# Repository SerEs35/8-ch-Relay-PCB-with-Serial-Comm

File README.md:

# 8-ch-Relay-PCB-with-Serial-Comm

About this project:
----
This was a project done during undergraduate studies. It is a PCB, operated by a 16F84A microcontroller connected to the computer via Serial Port. The relays can be activated from the computer, and it is only one-way transmission.

The documents in this repository are listed as follows:

\schema_8relay.sch
>Contains the schematic of the circuit, performed in Eagle Cadsoft

\schema_8relay.brd
>Contains the layout of the circuit, performed in Eagle Cadsoft

\project.asm
>Contains the source code in ASM language for the microcontroller

\Serial_rs232.zip
>Contains the source code project for the GUI coded in C# with MS Visual Studio 2003

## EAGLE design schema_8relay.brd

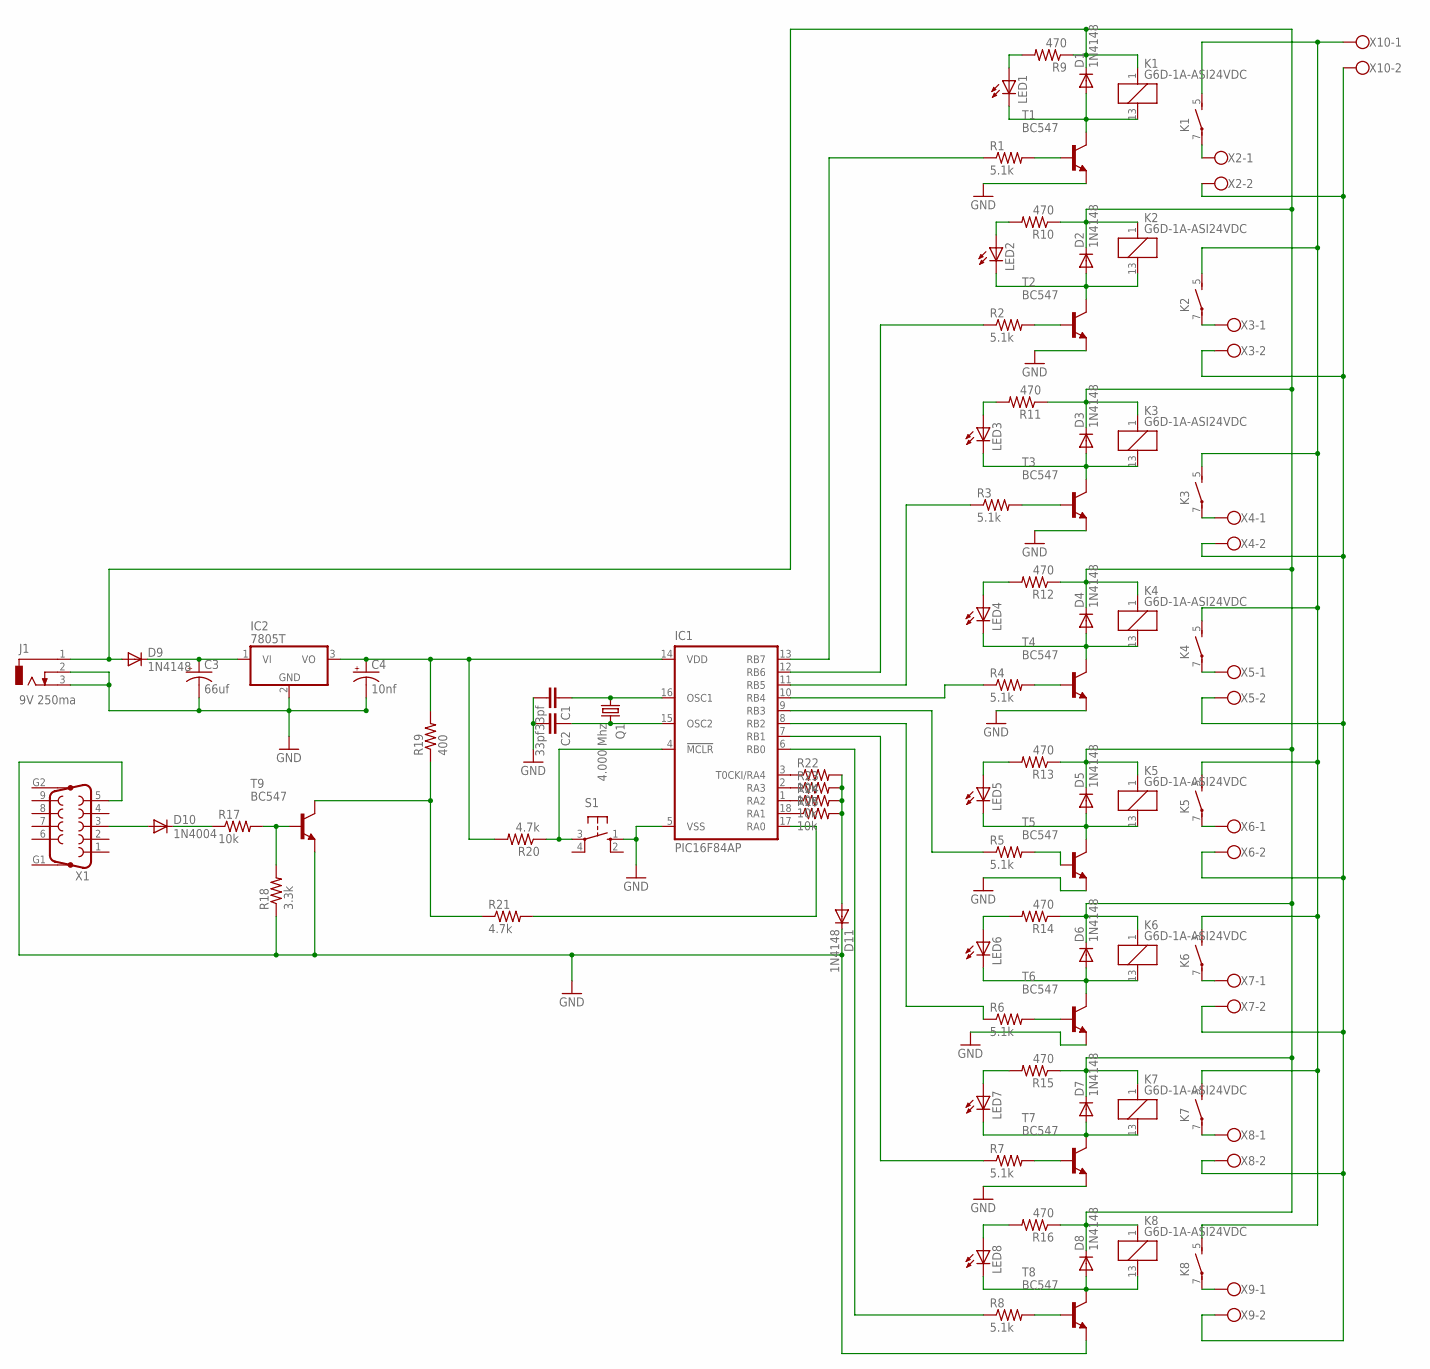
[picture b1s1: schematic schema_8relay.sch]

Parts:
C1, C2: 33pf; C050-024X044
C3: 66uf; E2,5-6
C4: 10nf; E2,5-6
D1, D2, D3, D4, D5, D6, D7, D8, D9, D11: 1N4148; DO35-10
D10: 1N4004; DO41-10
IC1: PIC16F84AP; DIL18
IC2: 7805T; TO220H
J1: 9V 250ma; DCJ0303
K1, K2, K3, K4, K5, K6, K7, K8: G6D-1A-ASI24VDC; G6D
LED1, LED2, LED3, LED4, LED5, LED6, LED7, LED8: LED3MM
Q1: 4.000 Mhz; HC49U70
R1, R2, R3, R4, R5, R6, R7, R8: 5.1k; 0204/7
R9, R10, R11, R12, R13, R14, R15, R16: 470; 0204/7
R17, R22, R23, R24, R25: 10k; 0204/7
R18: 3.3k; 0204/7
R19: 400; 0207/12
R20, R21: 4.7k; 0204/7
S1: 10-XX; B3F-10XX
T1, T2, T3, T4, T5, T6, T7, T8, T9: BC547; TO92
X1: F09HP
X2, X3, X4, X5, X6, X7, X8, X9, X10: W237-102

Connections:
GND: C1.2, C2.2, C3.-, C4.-, D11.C, IC1.5 (VSS), IC2.2 (GND), J1.2, J1.3, R18.1, S1.1 (S), T1.1 (E), T2.1 (E), T3.1 (E), T4.1 (E), T5.1 (E), T6.1 (E), T7.1 (E), T8.1 (E), T9.1 (E), X1.5
unnamed: C1.1, IC1.16 (OSC1), Q1.1
unnamed: C2.1, IC1.15 (OSC2), Q1.2
unnamed: R19.1, R21.1, T9.3 (C)
unnamed: D1.A, K1.13 (2), LED1.K (C), T1.3 (C)
unnamed: R1.2, T1.2 (B)
unnamed: D2.A, K2.13 (2), LED2.K (C), T2.3 (C)
unnamed: IC1.17 (RA0), R21.2
unnamed: IC1.4 (!MCLR), R20.1, S1.3
unnamed: D10.A, X1.3
unnamed: D10.C, R17.1
unnamed: R17.2, R18.2, T9.2 (B)
unnamed: C4.+, IC1.14 (VDD), IC2.3 (VO), R19.2, R20.2
unnamed: IC1.13 (RB7), R1.1
unnamed: K1.7, X2.1
unnamed: R2.2, T2.2 (B)
unnamed: LED2.A, R10.2
unnamed: D4.A, K4.13 (2), LED4.K (C), T4.3 (C)
unnamed: D6.A, K6.13 (2), LED6.K (C), T6.3 (C)
unnamed: LED4.A, R12.2
unnamed: K2.7, X3.1
unnamed: IC1.10 (RB4), R4.1
unnamed: R3.2, T3.2 (B)
unnamed: R5.2, T5.2 (B)
unnamed: LED5.A, R13.2
unnamed: K3.7, X4.1
unnamed: IC1.9 (RB3), R5.1
unnamed: R4.2, T4.2 (B)
unnamed: LED6.A, R14.2
unnamed: LED3.A, R11.2
unnamed: K4.7, X5.1
unnamed: K1.5 (S), K2.5 (S), K3.5 (S), K4.5 (S), K5.5 (S), K6.5 (S), K7.5 (S), K8.5 (S), X10.1
unnamed: C3.+, D9.C, IC2.1 (VI)
unnamed: K5.7, X6.1
unnamed: IC1.3 (T0CKI/RA4), R22.1
unnamed: R6.2, T6.2 (B)
unnamed: IC1.2 (RA3), R23.1
unnamed: K6.7, X7.1
unnamed: IC1.1 (RA2), R24.1
unnamed: R7.2, T7.2 (B)
unnamed: D7.A, K7.13 (2), LED7.K (C), T7.3 (C)
unnamed: IC1.18 (RA1), R25.1
unnamed: K7.7, X8.1
unnamed: D5.A, K5.13 (2), LED5.K (C), T5.3 (C)
unnamed: R8.2, T8.2 (B)
unnamed: LED8.A, R16.2
unnamed: LED7.A, R15.2
unnamed: K8.7, X9.1
unnamed: IC1.6 (RB0), R8.1
unnamed: IC1.7 (RB1), R7.1
unnamed: IC1.8 (RB2), R6.1
unnamed: D8.A, K8.13 (2), LED8.K (C), T8.3 (C)
unnamed: LED1.A, R9.2
unnamed: IC1.11 (RB5), R3.1
unnamed: IC1.12 (RB6), R2.1
unnamed: X2.2, X3.2, X4.2, X5.2, X6.2, X7.2, X8.2, X9.2, X10.2
unnamed: D1.C, D2.C, D3.C, D4.C, D5.C, D6.C, D7.C, D8.C, D9.A, J1.1, K1.1, K2.1, K3.1, K4.1, K5.1, K6.1, K7.1, K8.1, R9.1, R10.1, R11.1, R12.1, R13.1, R14.1, R15.1, R16.1
unnamed: D3.A, K3.13 (2), LED3.K (C), T3.3 (C)
unnamed: D11.A, R22.2, R23.2, R24.2, R25.2

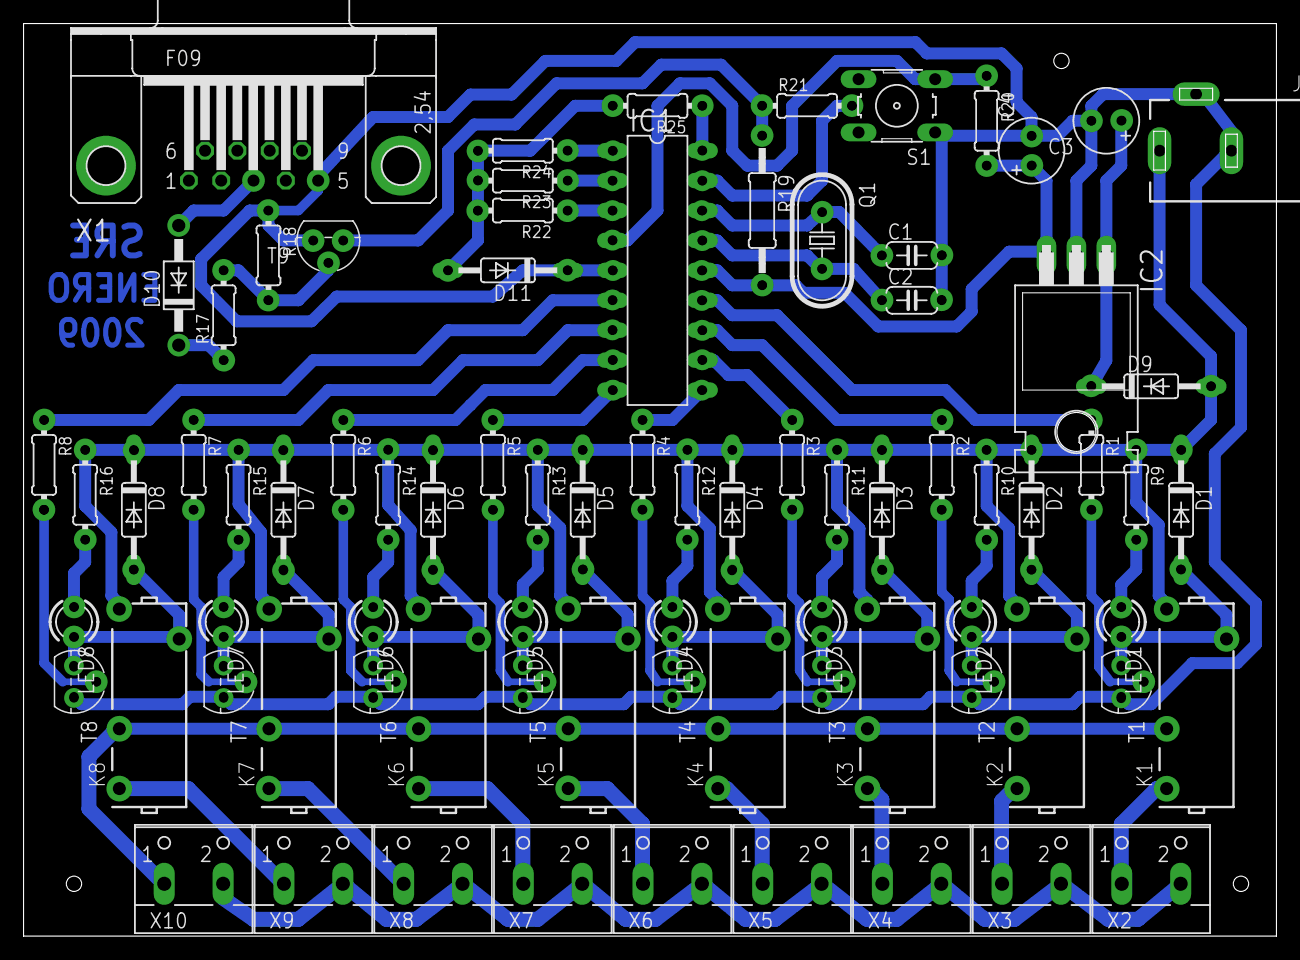
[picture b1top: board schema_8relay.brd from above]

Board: 2 copper layers, 106.3 x 77.5 mm, 80 parts (0 on the bottom side), 59 nets.
